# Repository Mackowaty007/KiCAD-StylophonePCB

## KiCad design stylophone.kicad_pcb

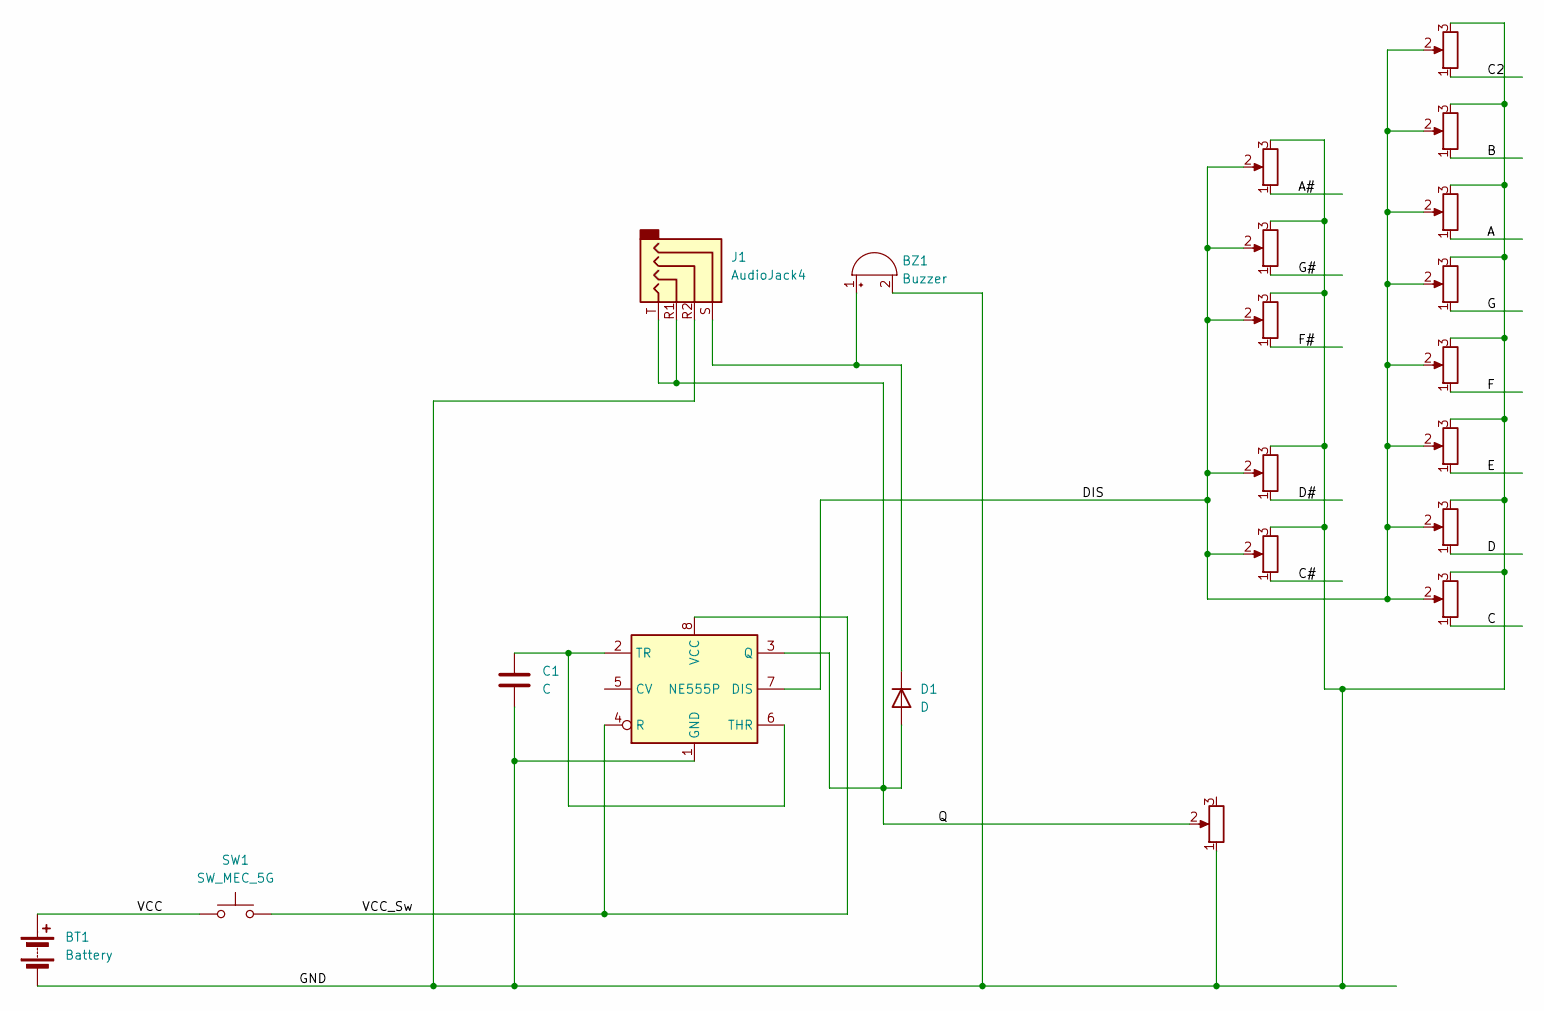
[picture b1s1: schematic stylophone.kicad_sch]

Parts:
BT1: Battery; BatteryHolder_ComfortableElectronic_CH273-2450_1x2450
BZ1: Buzzer; Buzzer_12x9.5RM7.6
C1: C; C_Radial_D6.3mm_H5.0mm_P2.50mm
D1: D; D_DO-201AE_P3.81mm_Vertical_AnodeUp
J1: AudioJack4; Jack_3.5mm_KoreanHropartsElec_PJ-320D-4A_Horizontal
RV2: R_Potentiometer; Potentiometer_Piher_PT-6-V_Vertical
RV_A1: R_Potentiometer; Potentiometer_Piher_PT-6-V_Vertical
RV_A#1: R_Potentiometer; Potentiometer_Piher_PT-6-V_Vertical
RV_B1: R_Potentiometer; Potentiometer_Piher_PT-6-V_Vertical
RV_C1, RV_C2: R_Potentiometer; Potentiometer_Piher_PT-6-V_Vertical
RV_C#1: R_Potentiometer; Potentiometer_Piher_PT-6-V_Vertical
RV_D1: R_Potentiometer; Potentiometer_Piher_PT-6-V_Vertical
RV_D#1: R_Potentiometer; Potentiometer_Piher_PT-6-V_Vertical
RV_E1: R_Potentiometer; Potentiometer_Piher_PT-6-V_Vertical
RV_F1: R_Potentiometer; Potentiometer_Piher_PT-6-V_Vertical
RV_F#1: R_Potentiometer; Potentiometer_Piher_PT-6-V_Vertical
RV_G1: R_Potentiometer; Potentiometer_Piher_PT-6-V_Vertical
RV_G#1: R_Potentiometer; Potentiometer_Piher_PT-6-V_Vertical
SW1: SW_MEC_5G; SW_Slide_1P2T_CK_OS102011MS2Q
U1: NE555P; DIP-8_W7.62mm

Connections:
/A: RV_A1.1
/A#: RV_A#1.1
/B: RV_B1.1
/C: RV_C1.1
/C2: RV_C2.1
/C#: RV_C#1.1
/D: RV_D1.1
/D#: RV_D#1.1
/DIS: RV_A1.2, RV_A#1.2, RV_B1.2, RV_C1.2, RV_C2.2, RV_C#1.2, RV_D1.2, RV_D#1.2, RV_E1.2, RV_F1.2, RV_F#1.2, RV_G1.2, RV_G#1.2, U1.7 (DIS)
/E: RV_E1.1
/F: RV_F1.1
/F#: RV_F#1.1
/G: RV_G1.1
/G#: RV_G#1.1
/GND: BT1.2 (-), BZ1.2 (+), C1.1, J1.R2, RV2.1, RV_A1.3, RV_A#1.3, RV_B1.3, RV_C1.3, RV_C2.3, RV_C#1.3, RV_D1.3, RV_D#1.3, RV_E1.3, RV_F1.3, RV_F#1.3, RV_G1.3, RV_G#1.3, U1.1 (GND)
/Q: D1.2 (A), J1.R1, J1.T, RV2.2, U1.3 (Q)
/VCC: BT1.1 (+), SW1.1 (A), SW1.2 (A)
/VCC_Sw: SW1.3 (B), SW1.4 (B), U1.4 (R), U1.8 (VCC)
unnamed: BZ1.1 (-), D1.1 (K), J1.S
unnamed: C1.2, U1.2 (TR), U1.6 (THR)

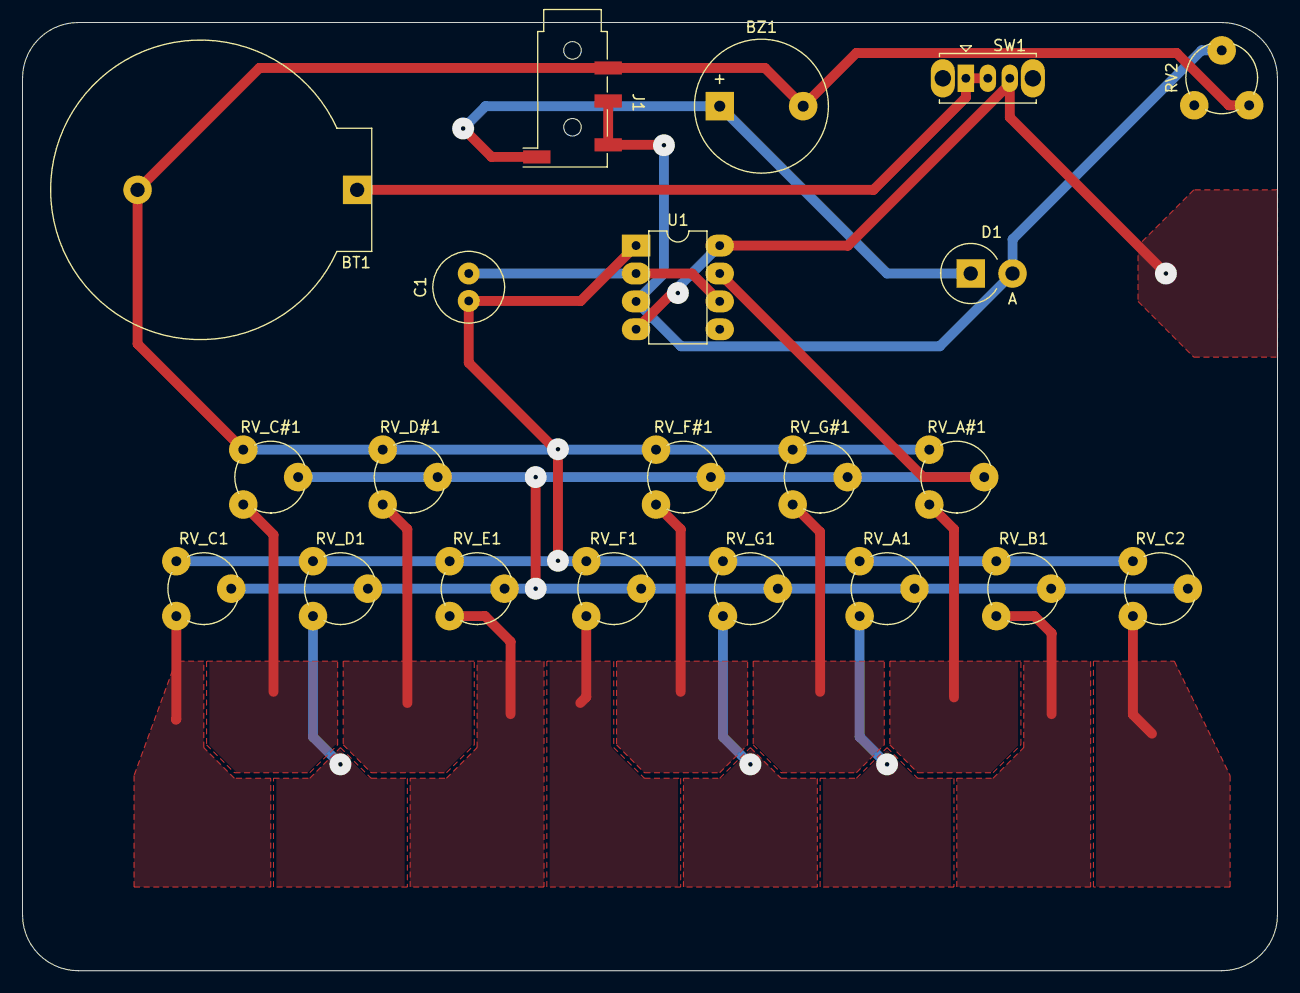
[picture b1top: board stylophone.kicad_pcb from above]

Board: 2 copper layers, 114.3 x 86.4 mm, 21 parts (0 on the bottom side), 7 nets.

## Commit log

2024-01-23 stuff
2024-01-23 herpderp
2024-01-23 gerber export
2024-01-24 solder mask keepouts
2024-01-24 ignore backups
